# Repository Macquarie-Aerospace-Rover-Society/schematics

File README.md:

# ALL THINGS ELECTRICAL
All the schematics and manufacturing files will be located here.

If there are any requests, corrections or objections, please direct them at @sunnyshenao on the MQ rover discord.

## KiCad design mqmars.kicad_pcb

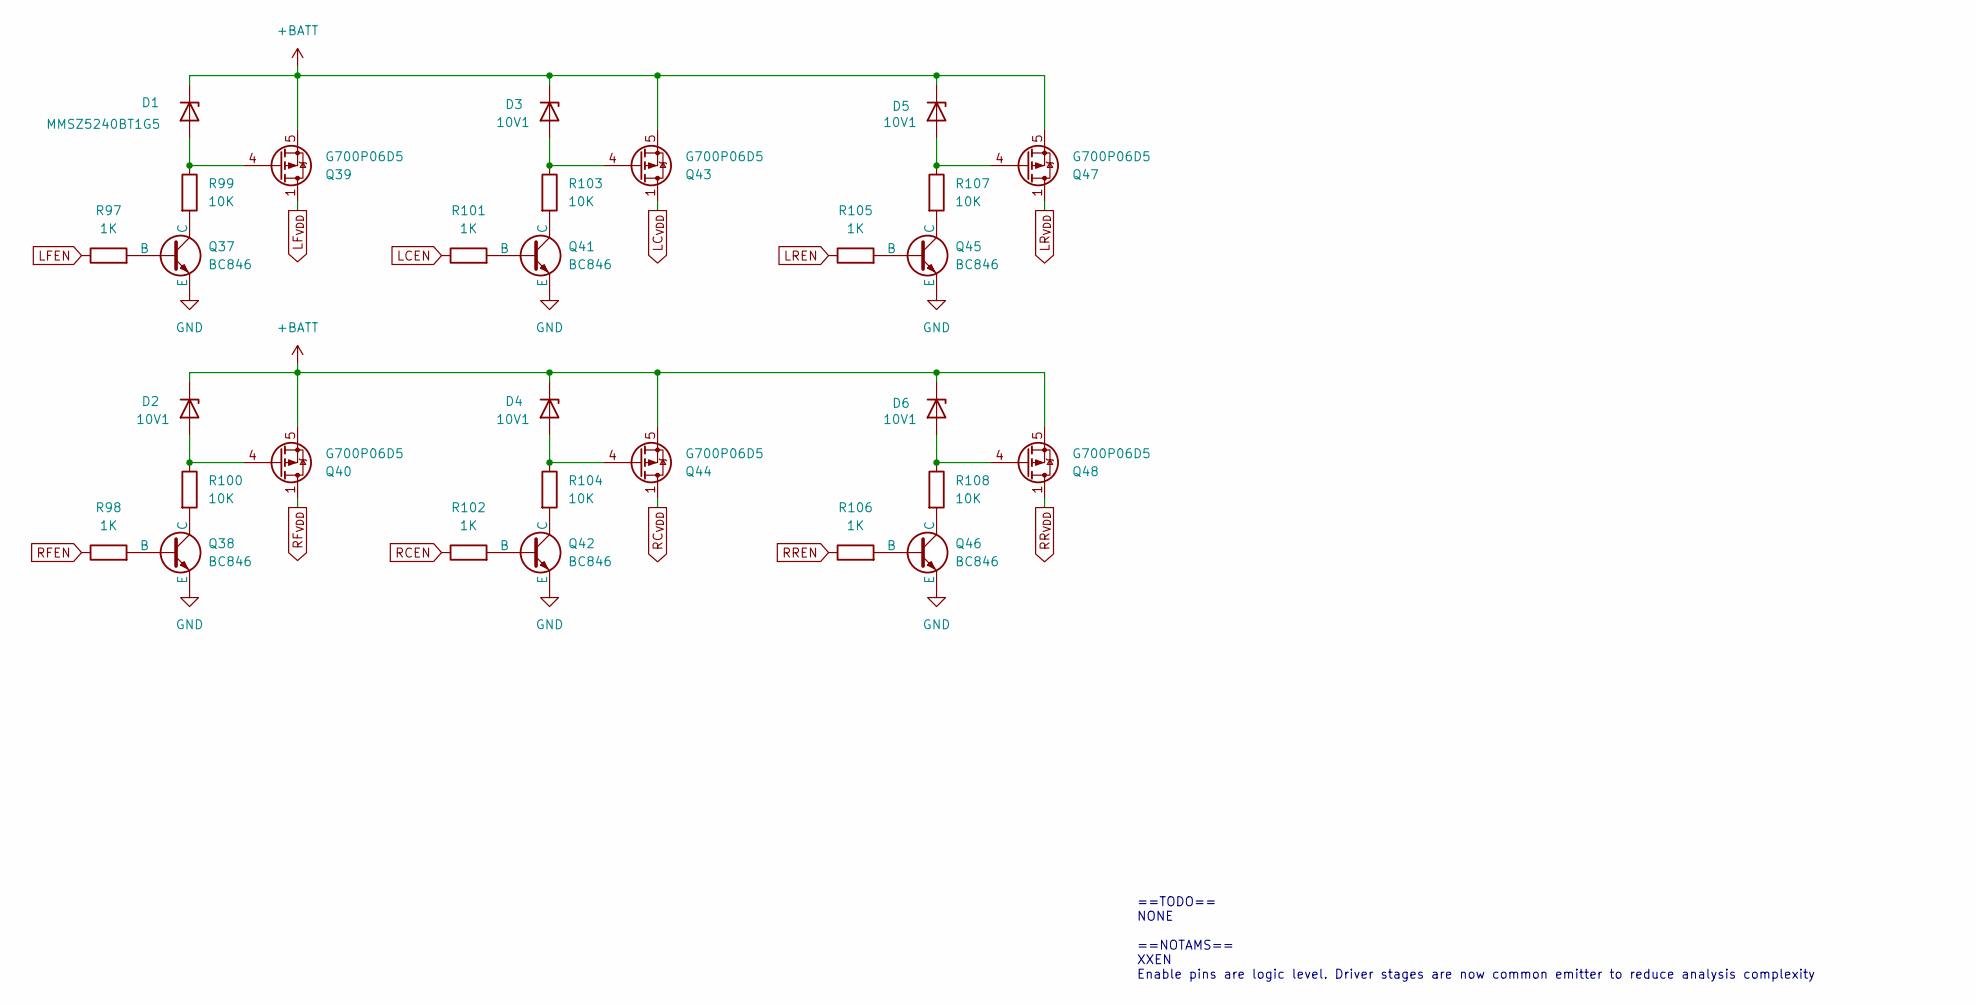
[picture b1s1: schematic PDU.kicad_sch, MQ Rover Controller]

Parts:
D1: MMSZ5240BT1G5; D_SOD-123
D2, D3, D4, D5, D6: 10V1; D_SOD-123
Q37, Q38, Q41, Q42, Q45, Q46: BC846; SOT-23
Q39, Q40, Q43, Q44, Q47, Q48: G700P06D5; PowerPAK_SO-8_Single
R97, R98, R101, R102, R105, R106: 1K; R_0201_0603Metric
R99, R100, R103, R104, R107, R108: 10K; R_1210_3225Metric

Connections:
+BATT: D1.1 (K), D2.1 (K), D3.1 (K), D4.1 (K), D5.1 (K), D6.1 (K), Q39.5 (S), Q40.5 (S), Q43.5 (S), Q44.5 (S), Q47.5 (S), Q48.5 (S); also elsewhere on the board
GND: Q37.3 (E), Q38.3 (E), Q41.3 (E), Q42.3 (E), Q45.3 (E), Q46.3 (E); also elsewhere on the board
LCEN: R101.1; also elsewhere on the board
LC_{VDD}: Q43.1 (D), Q43.2 (D), Q43.3 (D); also elsewhere on the board
LFEN: R97.1; also elsewhere on the board
LF_{VDD}: Q39.1 (D), Q39.2 (D), Q39.3 (D); also elsewhere on the board
LREN: R105.1; also elsewhere on the board
LR_{VDD}: Q47.1 (D), Q47.2 (D), Q47.3 (D); also elsewhere on the board
unnamed: D1.2 (A), Q39.4 (G), R99.1
unnamed: D2.2 (A), Q40.4 (G), R100.1
unnamed: D3.2 (A), Q43.4 (G), R103.1
unnamed: D4.2 (A), Q44.4 (G), R104.1
unnamed: D5.2 (A), Q47.4 (G), R107.1
unnamed: D6.2 (A), Q48.4 (G), R108.1
unnamed: Q37.2 (B), R97.2
unnamed: Q37.1 (C), R99.2
unnamed: Q38.2 (B), R98.2
unnamed: Q38.1 (C), R100.2
unnamed: Q41.2 (B), R101.2
unnamed: Q41.1 (C), R103.2
unnamed: Q42.2 (B), R102.2
unnamed: Q42.1 (C), R104.2
unnamed: Q45.2 (B), R105.2
unnamed: Q45.1 (C), R107.2
unnamed: Q46.2 (B), R106.2
unnamed: Q46.1 (C), R108.2
RCEN: R102.1; also elsewhere on the board
RC_{VDD}: Q44.1 (D), Q44.2 (D), Q44.3 (D); also elsewhere on the board
RFEN: R98.1; also elsewhere on the board
RF_{VDD}: Q40.1 (D), Q40.2 (D), Q40.3 (D); also elsewhere on the board
RREN: R106.1; also elsewhere on the board
RR_{VDD}: Q48.1 (D), Q48.2 (D), Q48.3 (D); also elsewhere on the board

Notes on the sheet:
==TODO== NONE ==NOTAMS== XXEN Enable pins are logic level. Driver stages are now common emitter to reduce analysis complexity

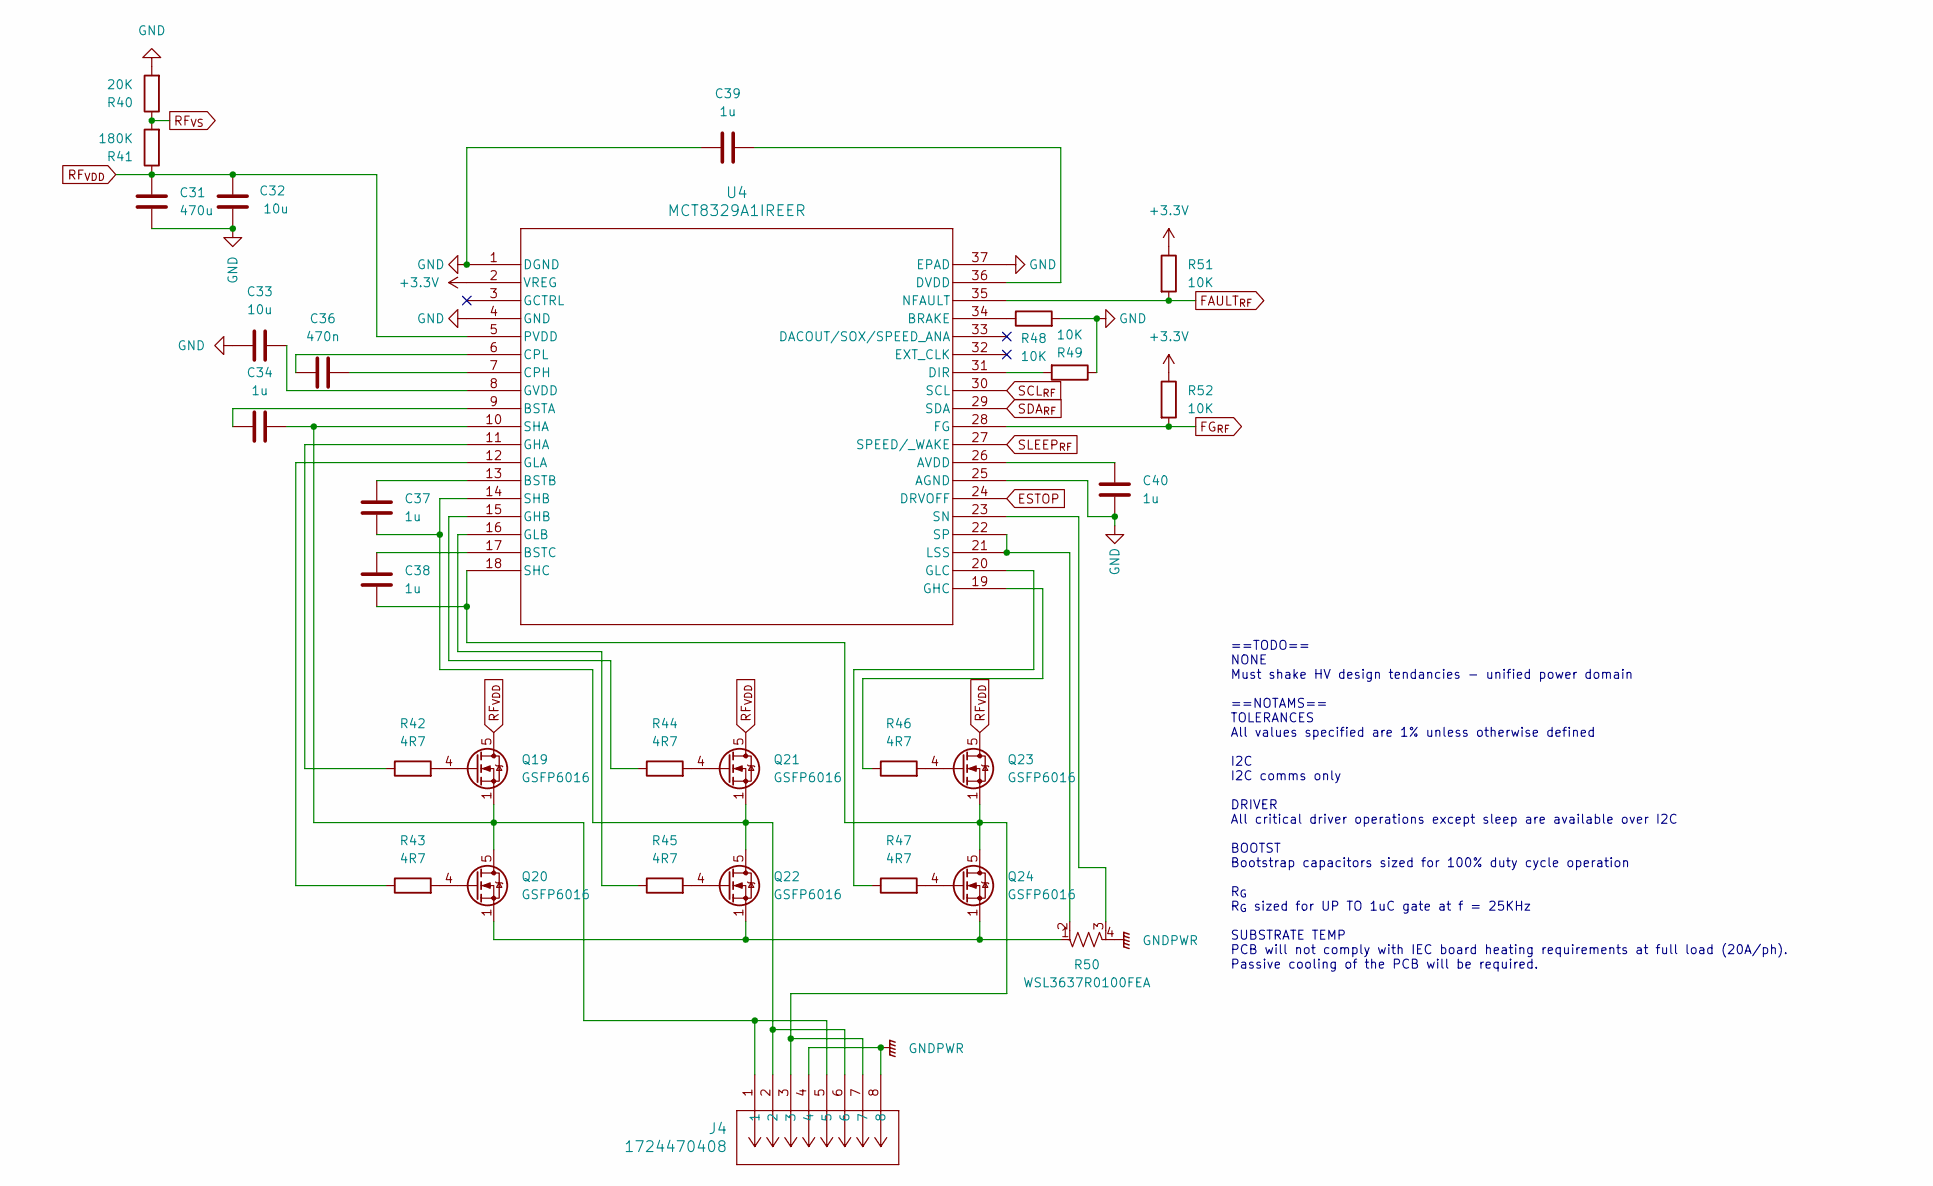
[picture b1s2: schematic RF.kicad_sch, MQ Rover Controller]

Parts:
C31: 470u; CP_Radial_D10.0mm_P5.00mm
C32: 10u; C_1210_3225Metric
C33: 10u; C_0402_1005Metric
C34, C37, C38, C39, C40: 1u; C_0201_0603Metric
C36: 470n; C_0201_0603Metric
J4: 1724470408; CONN08_1724470408_MOL
Q19, Q20, Q21, Q22, Q23, Q24: GSFP6016; PowerPAK_SO-8_Single
R40: 20K; R_0201_0603Metric
R41: 180K; R_0201_0603Metric
R42, R43, R44, R45, R46, R47: 4R7; R_0603_1608Metric
R48, R49, R51, R52: 10K; R_0201_0603Metric
R50: WSL3637R0100FEA; WSL3637_VIS
U4: MCT8329A1IREER; WQFN36_REE_TEX

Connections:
+3.3V: R51.1, R52.1, U4.2 (VREG); also elsewhere on the board
ESTOP: U4.24 (DRVOFF); also elsewhere on the board
FAULT_{RF}: R51.2, U4.35 (NFAULT); also elsewhere on the board
FG_{RF}: R52.2, U4.28 (FG)
GND: C31.2, C32.2, C33.1, C39.1, C40.1, R40.2, R48.2, R49.1, U4.1 (DGND), U4.4 (GND), U4.25 (AGND), U4.37 (EPAD); also elsewhere on the board
GNDPWR: J4.4, J4.8, R50.4; also elsewhere on the board
unnamed: Q19.4 (G), R42.2
unnamed: C34.1, J4.1, J4.5, Q19.1 (S), Q19.2 (S), Q19.3 (S), Q20.5 (D), U4.10 (SHA)
unnamed: Q20.4 (G), R43.2
unnamed: Q20.1 (S), Q20.2 (S), Q20.3 (S), Q22.1 (S), Q22.2 (S), Q22.3 (S), Q24.1 (S), Q24.2 (S), Q24.3 (S), R50.1
unnamed: Q21.4 (G), R44.2
unnamed: C37.2, J4.2, J4.6, Q21.1 (S), Q21.2 (S), Q21.3 (S), Q22.5 (D), U4.14 (SHB)
unnamed: Q22.4 (G), R45.2
unnamed: Q23.4 (G), R46.2
unnamed: C38.2, J4.3, J4.7, Q23.1 (S), Q23.2 (S), Q23.3 (S), Q24.5 (D), U4.18 (SHC)
unnamed: Q24.4 (G), R47.2
unnamed: C40.2, U4.26 (AVDD)
unnamed: R48.1, U4.34 (BRAKE)
unnamed: C34.2, U4.9 (BSTA)
unnamed: C37.1, U4.13 (BSTB)
unnamed: C38.1, U4.17 (BSTC)
unnamed: C36.1, U4.7 (CPH)
unnamed: C36.2, U4.6 (CPL)
unnamed: R49.2, U4.31 (DIR)
unnamed: C39.2, U4.36 (DVDD)
unnamed: R42.1, U4.11 (GHA)
unnamed: R44.1, U4.15 (GHB)
unnamed: R46.1, U4.19 (GHC)
unnamed: R43.1, U4.12 (GLA)
unnamed: R45.1, U4.16 (GLB)
unnamed: R47.1, U4.20 (GLC)
unnamed: C33.2, U4.8 (GVDD)
unnamed: R50.2, U4.21 (LSS), U4.22 (SP)
unnamed: R50.3, U4.23 (SN)
RF_{VDD}: C31.1, C32.1, Q19.5 (D), Q21.5 (D), Q23.5 (D), R41.1, U4.5 (PVDD); also elsewhere on the board
RF_{VS}: R40.1, R41.2; also elsewhere on the board
SCL_{RF}: U4.30 (SCL); also elsewhere on the board
SDA_{RF}: U4.29 (SDA); also elsewhere on the board
SLEEP_{RF}: U4.27 (SPEED/_WAKE)

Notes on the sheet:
==TODO== NONE Must shake HV design tendancies - unified power domain ==NOTAMS== TOLERANCES All values specified are 1% unless otherwise defined I2C I2C comms only DRIVER All critical driver operations except sleep are available over I2C BOOTST Bootstrap capacitors sized for 100% duty cycle operatio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

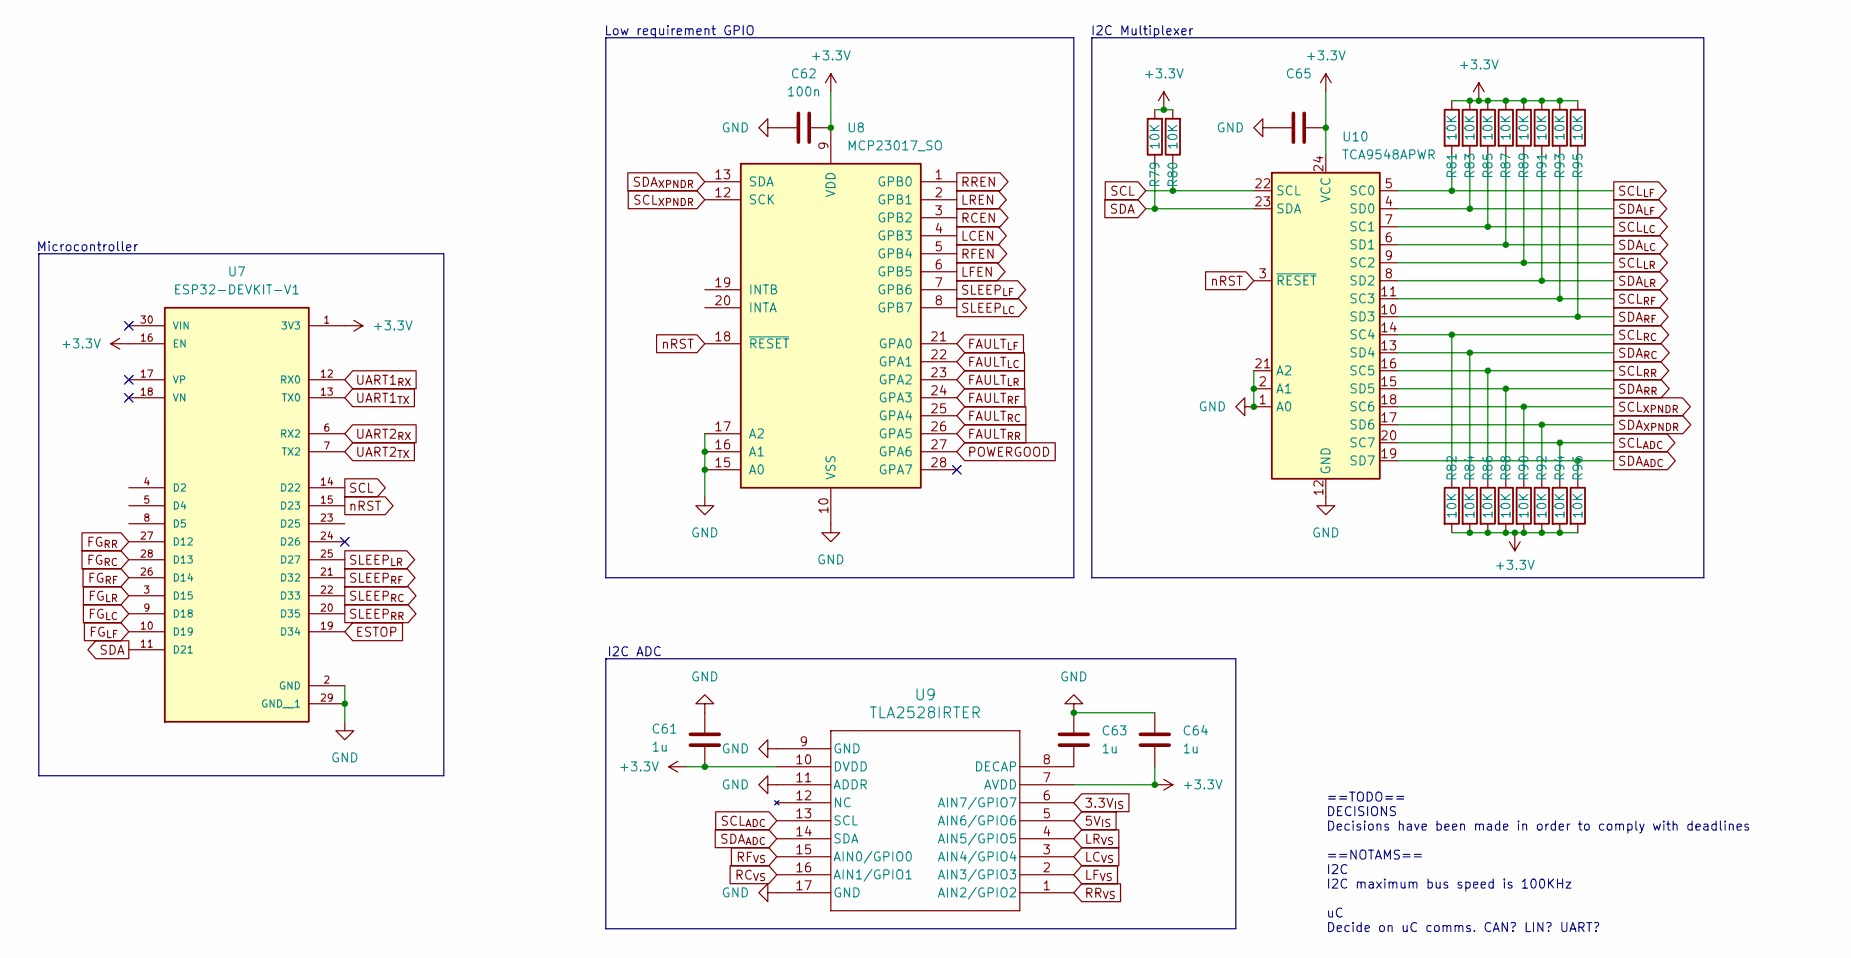
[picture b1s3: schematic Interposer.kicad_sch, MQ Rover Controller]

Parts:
C61, C63, C64: 1u; C_0201_0603Metric
C62: 100n; C_0201_0603Metric
C65: C_0201_0603Metric
R79, R80, R81, R82, R83, R84, R85, R86, R87, R88, R89, R90, R91, R92, R93, R94, R95, R96: 10K; R_0201_0603Metric
U7: ESP32-DEVKIT-V1; MODULE_ESP32_DEVKIT_V1; PARTREV N/A
U8: MCP23017_SO; SOIC-28W_7.5x17.9mm_P1.27mm
U9: TLA2528IRTER; WQFN16_RTE_TEX
U10: TCA9548APWR; TSSOP-24_4.4x7.8mm_P0.65mm

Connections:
3.3V_{IS}: U9.6 (AIN7/GPIO7); also elsewhere on the board
5V_{IS}: U9.5 (AIN6/GPIO6); also elsewhere on the board
+3.3V: C61.1, C62.2, C64.2, C65.2, R79.2, R80.2, R81.1, R82.2, R83.1, R84.2, R85.1, R86.2, R87.1, R88.2, R89.1, R90.2, R91.1, R92.2, R93.1, R94.2, R95.1, R96.2, U7.1 (3V3), U7.16 (EN), U8.9 (VDD), U9.7 (AVDD), U9.10 (DVDD), U10.24 (VCC); also elsewhere on the board
FAULT_{LC}: U8.22 (GPA1); also elsewhere on the board
FAULT_{LF}: U8.21 (GPA0); also elsewhere on the board
FAULT_{LR}: U8.23 (GPA2); also elsewhere on the board
FAULT_{RC}: U8.25 (GPA4); also elsewhere on the board
FAULT_{RF}: U8.24 (GPA3); also elsewhere on the board
FAULT_{RR}: U8.26 (GPA5); also elsewhere on the board
GND: C61.2, C62.1, C63.1, C64.1, C65.1, U7.2 (GND), U7.29 (GND__1), U8.10 (VSS), U8.15 (A0), U8.16 (A1), U8.17 (A2), U9.9 (GND), U9.11 (ADDR), U9.17 (GND), U10.1 (A0), U10.2 (A1), U10.12 (GND), U10.21 (A2); also elsewhere on the board
LCEN: U8.4 (GPB3); also elsewhere on the board
LC_{VS}: U9.3 (AIN4/GPIO4); also elsewhere on the board
LFEN: U8.6 (GPB5); also elsewhere on the board
LF_{VS}: U9.2 (AIN3/GPIO3); also elsewhere on the board
LREN: U8.2 (GPB1); also elsewhere on the board
LR_{VS}: U9.4 (AIN5/GPIO5); also elsewhere on the board
unnamed: C63.2, U9.8 (DECAP)
POWERGOOD: U8.27 (GPA6); also elsewhere on the board
RCEN: U8.3 (GPB2); also elsewhere on the board
RC_{VS}: U9.16 (AIN1/GPIO1); also elsewhere on the board
RFEN: U8.5 (GPB4); also elsewhere on the board
RF_{VS}: U9.15 (AIN0/GPIO0); also elsewhere on the board
RREN: U8.1 (GPB0); also elsewhere on the board
RR_{VS}: U9.1 (AIN2/GPIO2); also elsewhere on the board
SCL: R80.1, U7.14 (D22), U10.22 (SCL)
SCL_{ADC}: R94.1, U9.13 (SCL), U10.20 (SC7)
SCL_{LC}: R85.2, U10.7 (SC1); also elsewhere on the board
SCL_{LF}: R81.2, U10.5 (SC0); also elsewhere on the board
SCL_{LR}: R89.2, U10.9 (SC2); also elsewhere on the board
SCL_{RC}: R82.1, U10.14 (SC4); also elsewhere on the board
SCL_{RF}: R93.2, U10.11 (SC3); also elsewhere on the board
SCL_{RR}: R86.1, U10.16 (SC5); also elsewhere on the board
SCL_{XPNDR}: R90.1, U8.12 (SCK), U10.18 (SC6)
SDA: R79.1, U7.11 (D21), U10.23 (SDA)
SDA_{ADC}: R96.1, U9.14 (SDA), U10.19 (SD7)
SDA_{LC}: R87.2, U10.6 (SD1); also elsewhere on the board
SDA_{LF}: R83.2, U10.4 (SD0); also elsewhere on the board
SDA_{LR}: R91.2, U10.8 (SD2); also elsewhere on the board
SDA_{RC}: R84.1, U10.13 (SD4); also elsewhere on the board
SDA_{RF}: R95.2, U10.10 (SD3); also elsewhere on the board
SDA_{RR}: R88.1, U10.15 (SD5); also elsewhere on the board
SDA_{XPNDR}: R92.1, U8.13 (SDA), U10.17 (SD6)
SLEEP_{LC}: U8.8 (GPB7); also elsewhere on the board
SLEEP_{LF}: U8.7 (GPB6); also elsewhere on the board
nRST: U7.15 (D23), U8.18 (~RESET), U10.3 (~RESET)

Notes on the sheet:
==TODO== DECISIONS Decisions have been made in order to comply with deadlines ==NOTAMS== I2C I2C maximum bus speed is 100KHz uC Decide on uC comms. CAN? LIN? UART?
I2C Multiplexer
Microcontroller
Low requirement GPIO
I2C ADC

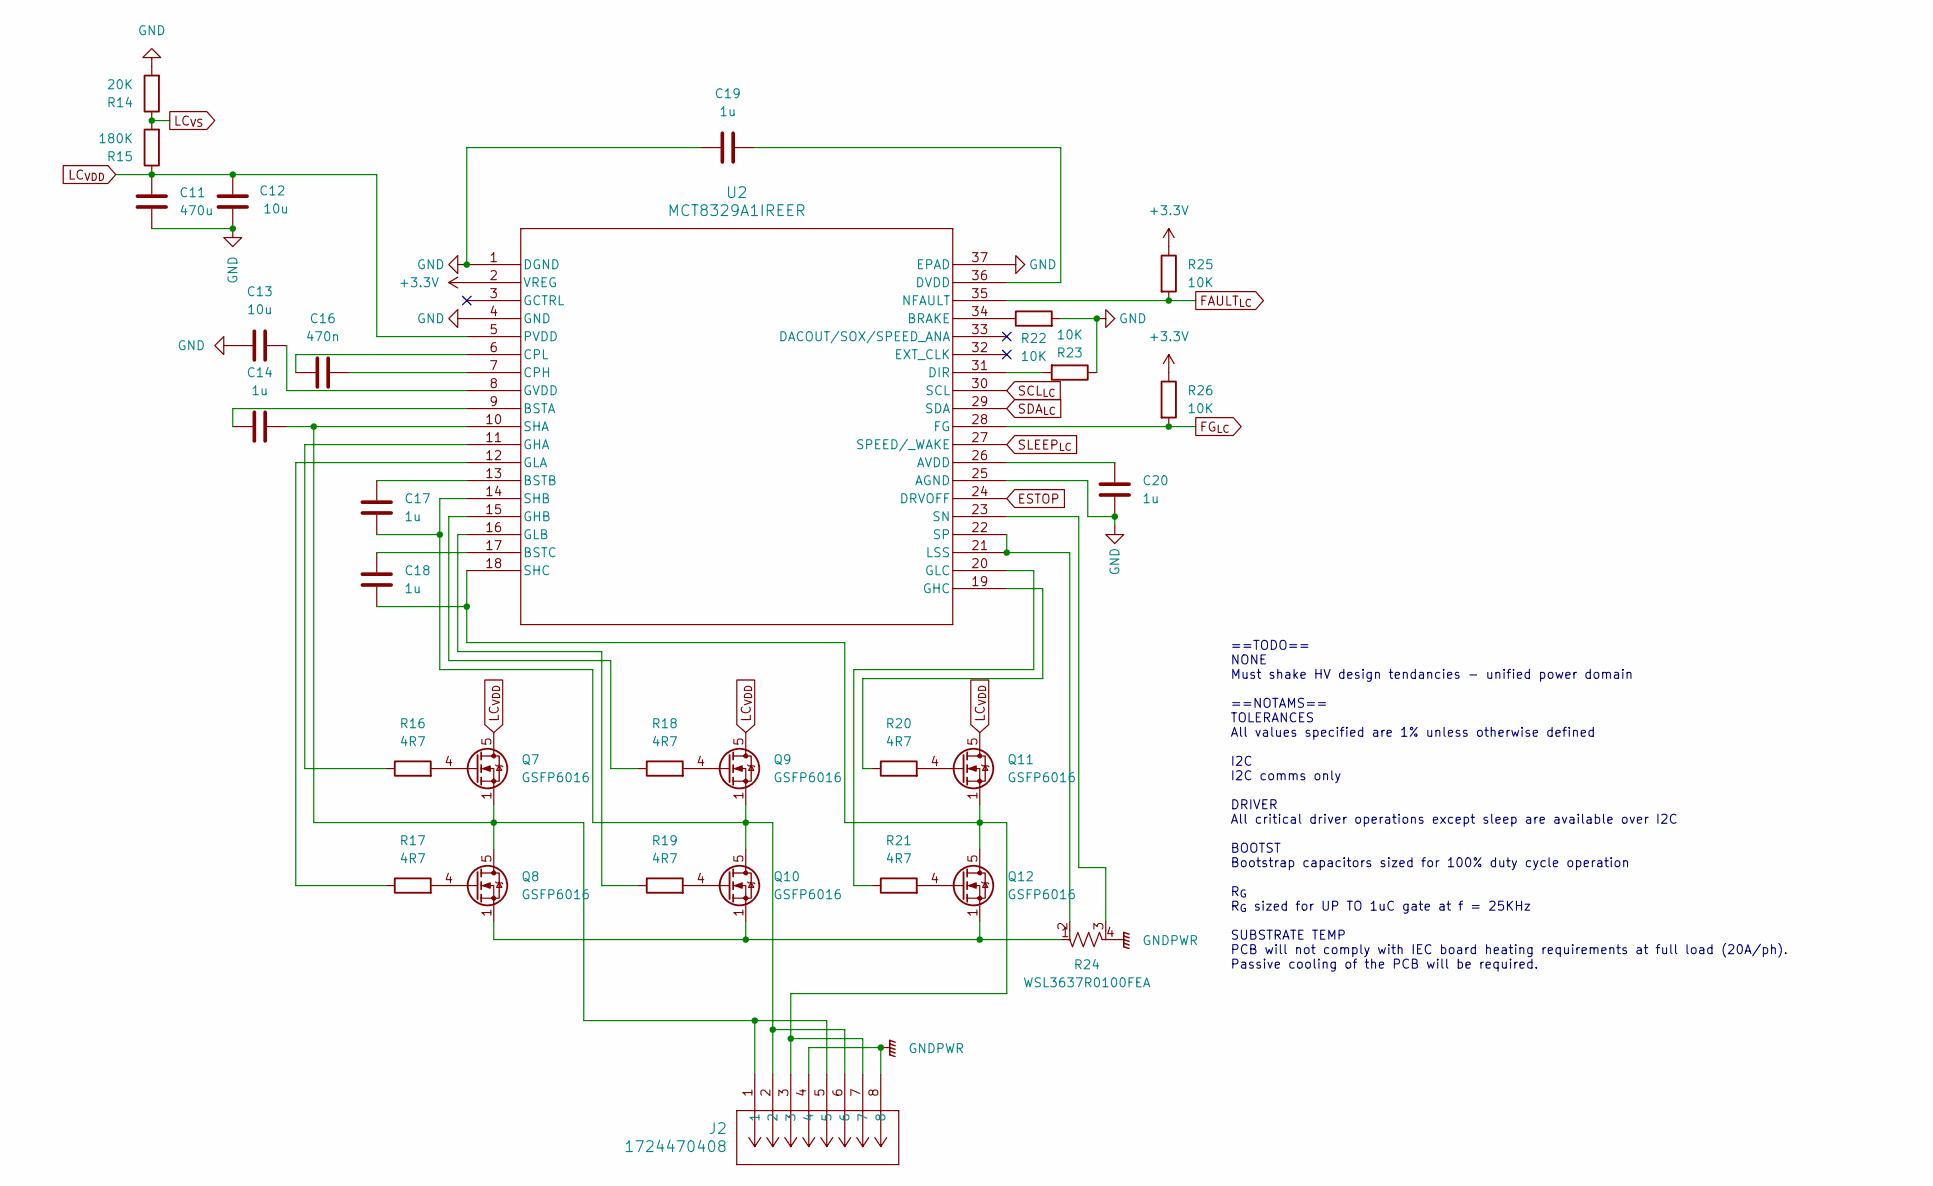
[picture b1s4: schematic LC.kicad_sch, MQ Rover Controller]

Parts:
C11: 470u; CP_Radial_D10.0mm_P5.00mm
C12: 10u; C_1210_3225Metric
C13: 10u; C_0402_1005Metric
C14, C17, C18, C19, C20: 1u; C_0201_0603Metric
C16: 470n; C_0201_0603Metric
J2: 1724470408; CONN08_1724470408_MOL
Q7, Q8, Q9, Q10, Q11, Q12: GSFP6016; PowerPAK_SO-8_Single
R14: 20K; R_0201_0603Metric
R15: 180K; R_0201_0603Metric
R16, R17, R18, R19, R20, R21: 4R7; R_0603_1608Metric
R22, R23, R25, R26: 10K; R_0201_0603Metric
R24: WSL3637R0100FEA; WSL3637_VIS
U2: MCT8329A1IREER; WQFN36_REE_TEX

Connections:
+3.3V: R25.1, R26.1, U2.2 (VREG); also elsewhere on the board
ESTOP: U2.24 (DRVOFF); also elsewhere on the board
FAULT_{LC}: R25.2, U2.35 (NFAULT); also elsewhere on the board
FG_{LC}: R26.2, U2.28 (FG)
GND: C11.2, C12.2, C13.1, C19.1, C20.1, R14.2, R22.2, R23.1, U2.1 (DGND), U2.4 (GND), U2.25 (AGND), U2.37 (EPAD); also elsewhere on the board
GNDPWR: J2.4, J2.8, R24.4; also elsewhere on the board
LC_{VDD}: C11.1, C12.1, Q7.5 (D), Q9.5 (D), Q11.5 (D), R15.1, U2.5 (PVDD); also elsewhere on the board
LC_{VS}: R14.1, R15.2; also elsewhere on the board
unnamed: Q7.4 (G), R16.2
unnamed: C14.1, J2.1, J2.5, Q7.1 (S), Q7.2 (S), Q7.3 (S), Q8.5 (D), U2.10 (SHA)
unnamed: Q8.4 (G), R17.2
unnamed: Q9.4 (G), R18.2
unnamed: C17.2, J2.2, J2.6, Q9.1 (S), Q9.2 (S), Q9.3 (S), Q10.5 (D), U2.14 (SHB)
unnamed: Q10.4 (G), R19.2
unnamed: Q8.1 (S), Q8.2 (S), Q8.3 (S), Q10.1 (S), Q10.2 (S), Q10.3 (S), Q12.1 (S), Q12.2 (S), Q12.3 (S), R24.1
unnamed: Q11.4 (G), R20.2
unnamed: C18.2, J2.3, J2.7, Q11.1 (S), Q11.2 (S), Q11.3 (S), Q12.5 (D), U2.18 (SHC)
unnamed: Q12.4 (G), R21.2
unnamed: C20.2, U2.26 (AVDD)
unnamed: R22.1, U2.34 (BRAKE)
unnamed: C14.2, U2.9 (BSTA)
unnamed: C17.1, U2.13 (BSTB)
unnamed: C18.1, U2.17 (BSTC)
unnamed: C16.1, U2.7 (CPH)
unnamed: C16.2, U2.6 (CPL)
unnamed: R23.2, U2.31 (DIR)
unnamed: C19.2, U2.36 (DVDD)
unnamed: R16.1, U2.11 (GHA)
unnamed: R18.1, U2.15 (GHB)
unnamed: R20.1, U2.19 (GHC)
unnamed: R17.1, U2.12 (GLA)
unnamed: R19.1, U2.16 (GLB)
unnamed: R21.1, U2.20 (GLC)
unnamed: C13.2, U2.8 (GVDD)
unnamed: R24.2, U2.21 (LSS), U2.22 (SP)
unnamed: R24.3, U2.23 (SN)
SCL_{LC}: U2.30 (SCL); also elsewhere on the board
SDA_{LC}: U2.29 (SDA); also elsewhere on the board
SLEEP_{LC}: U2.27 (SPEED/_WAKE); also elsewhere on the board

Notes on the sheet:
==TODO== NONE Must shake HV design tendancies - unified power domain ==NOTAMS== TOLERANCES All values specified are 1% unless otherwise defined I2C I2C comms only DRIVER All critical driver operations except sleep are available over I2C BOOTST Bootstrap capacitors sized for 100% duty cycle operatio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

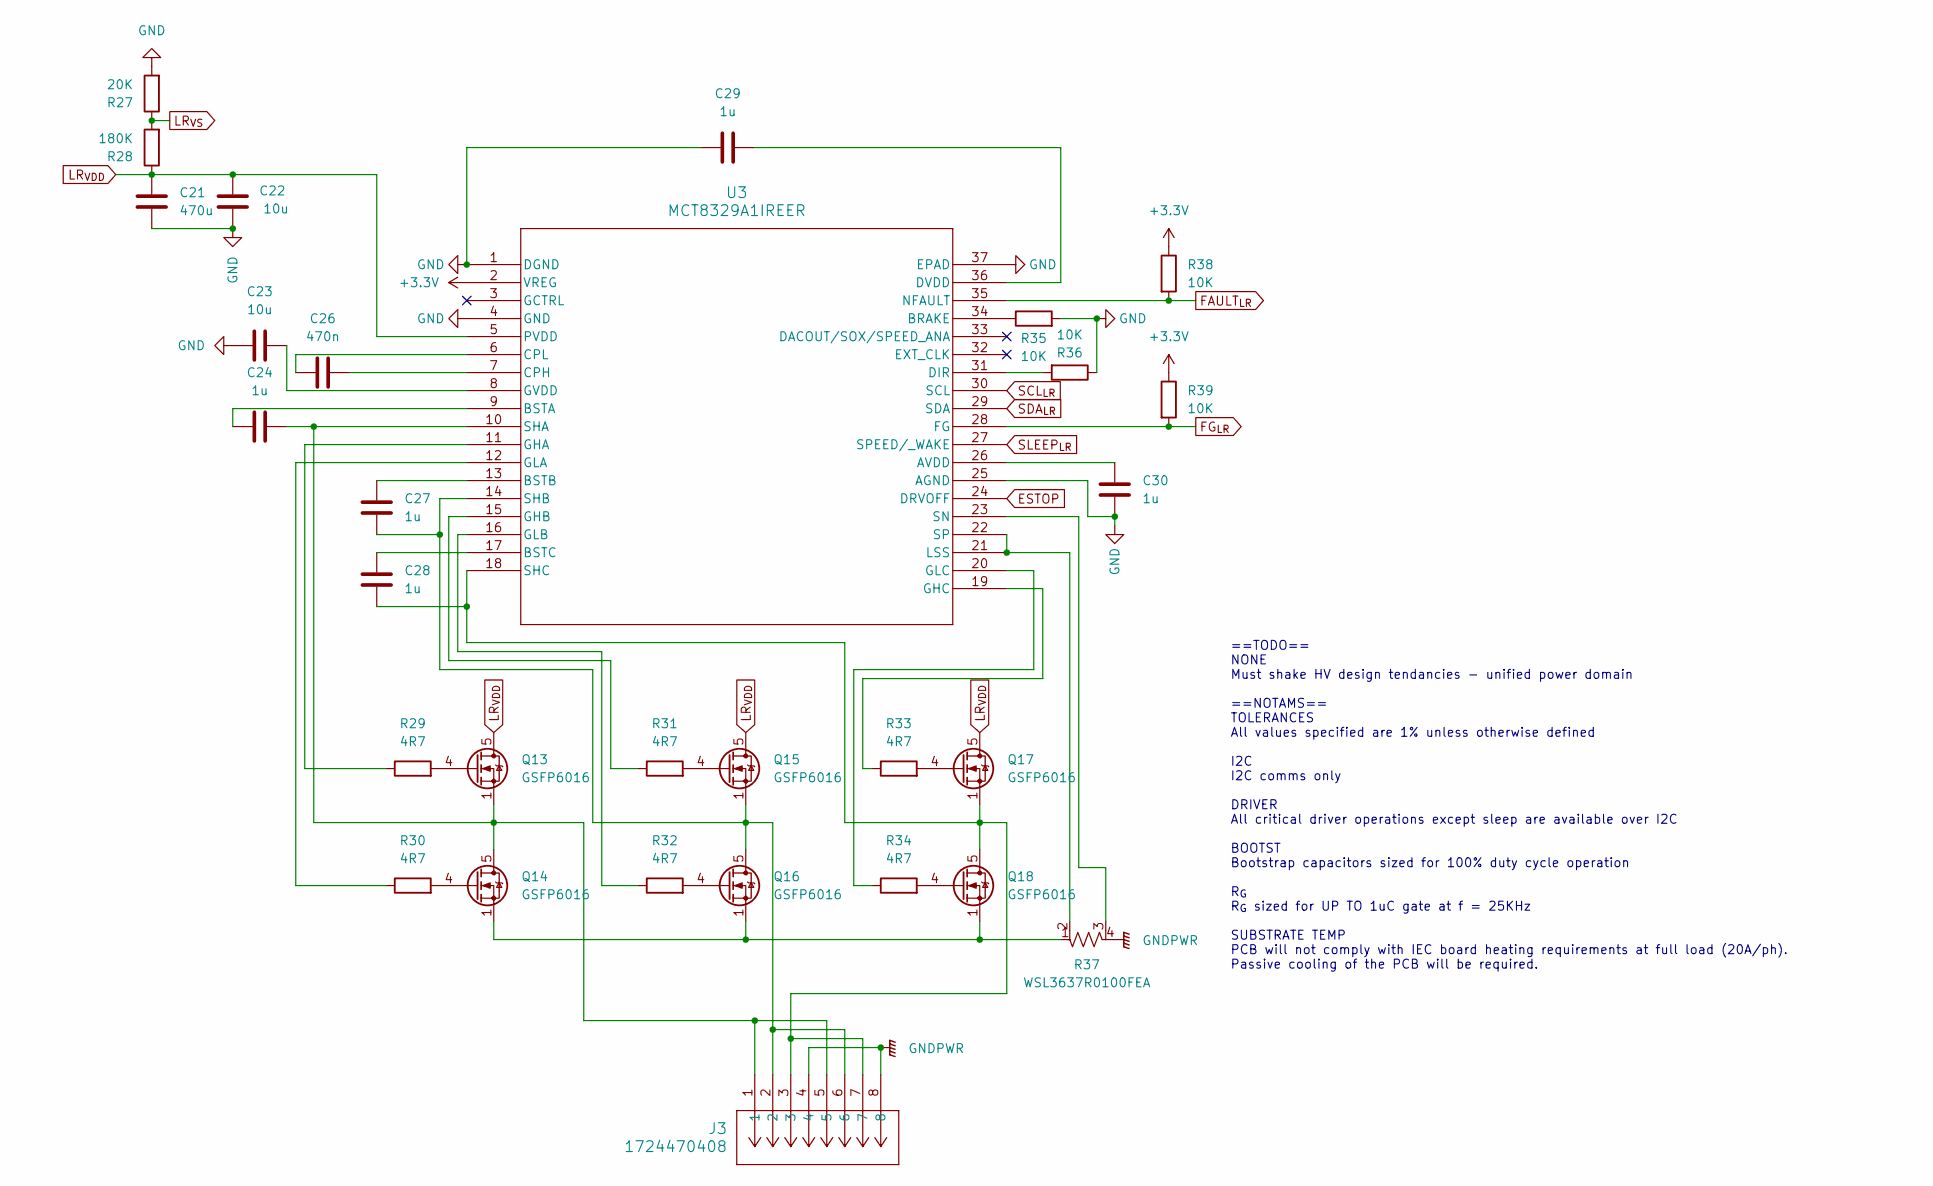
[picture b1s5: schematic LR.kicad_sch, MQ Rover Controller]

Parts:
C21: 470u; CP_Radial_D10.0mm_P5.00mm
C22: 10u; C_1210_3225Metric
C23: 10u; C_0402_1005Metric
C24, C27, C28, C29, C30: 1u; C_0201_0603Metric
C26: 470n; C_0201_0603Metric
J3: 1724470408; CONN08_1724470408_MOL
Q13, Q14, Q15, Q16, Q17, Q18: GSFP6016; PowerPAK_SO-8_Single
R27: 20K; R_0201_0603Metric
R28: 180K; R_0201_0603Metric
R29, R30, R31, R32, R33, R34: 4R7; R_0603_1608Metric
R35, R36, R38, R39: 10K; R_0201_0603Metric
R37: WSL3637R0100FEA; WSL3637_VIS
U3: MCT8329A1IREER; WQFN36_REE_TEX

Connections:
+3.3V: R38.1, R39.1, U3.2 (VREG); also elsewhere on the board
ESTOP: U3.24 (DRVOFF); also elsewhere on the board
FAULT_{LR}: R38.2, U3.35 (NFAULT); also elsewhere on the board
FG_{LR}: R39.2, U3.28 (FG)
GND: C21.2, C22.2, C23.1, C29.1, C30.1, R27.2, R35.2, R36.1, U3.1 (DGND), U3.4 (GND), U3.25 (AGND), U3.37 (EPAD); also elsewhere on the board
GNDPWR: J3.4, J3.8, R37.4; also elsewhere on the board
LR_{VDD}: C21.1, C22.1, Q13.5 (D), Q15.5 (D), Q17.5 (D), R28.1, U3.5 (PVDD); also elsewhere on the board
LR_{VS}: R27.1, R28.2; also elsewhere on the board
unnamed: Q13.4 (G), R29.2
unnamed: C24.1, J3.1, J3.5, Q13.1 (S), Q13.2 (S), Q13.3 (S), Q14.5 (D), U3.10 (SHA)
unnamed: Q14.4 (G), R30.2
unnamed: Q14.1 (S), Q14.2 (S), Q14.3 (S), Q16.1 (S), Q16.2 (S), Q16.3 (S), Q18.1 (S), Q18.2 (S), Q18.3 (S), R37.1
unnamed: Q15.4 (G), R31.2
unnamed: C27.2, J3.2, J3.6, Q15.1 (S), Q15.2 (S), Q15.3 (S), Q16.5 (D), U3.14 (SHB)
unnamed: Q16.4 (G), R32.2
unnamed: Q17.4 (G), R33.2
unnamed: C28.2, J3.3, J3.7, Q17.1 (S), Q17.2 (S), Q17.3 (S), Q18.5 (D), U3.18 (SHC)
unnamed: Q18.4 (G), R34.2
unnamed: C30.2, U3.26 (AVDD)
unnamed: R35.1, U3.34 (BRAKE)
unnamed: C24.2, U3.9 (BSTA)
unnamed: C27.1, U3.13 (BSTB)
unnamed: C28.1, U3.17 (BSTC)
unnamed: C26.1, U3.7 (CPH)
unnamed: C26.2, U3.6 (CPL)
unnamed: R36.2, U3.31 (DIR)
unnamed: C29.2, U3.36 (DVDD)
unnamed: R29.1, U3.11 (GHA)
unnamed: R31.1, U3.15 (GHB)
unnamed: R33.1, U3.19 (GHC)
unnamed: R30.1, U3.12 (GLA)
unnamed: R32.1, U3.16 (GLB)
unnamed: R34.1, U3.20 (GLC)
unnamed: C23.2, U3.8 (GVDD)
unnamed: R37.2, U3.21 (LSS), U3.22 (SP)
unnamed: R37.3, U3.23 (SN)
SCL_{LR}: U3.30 (SCL); also elsewhere on the board
SDA_{LR}: U3.29 (SDA); also elsewhere on the board
SLEEP_{LR}: U3.27 (SPEED/_WAKE)

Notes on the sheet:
==TODO== NONE Must shake HV design tendancies - unified power domain ==NOTAMS== TOLERANCES All values specified are 1% unless otherwise defined I2C I2C comms only DRIVER All critical driver operations except sleep are available over I2C BOOTST Bootstrap capacitors sized for 100% duty cycle operatio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

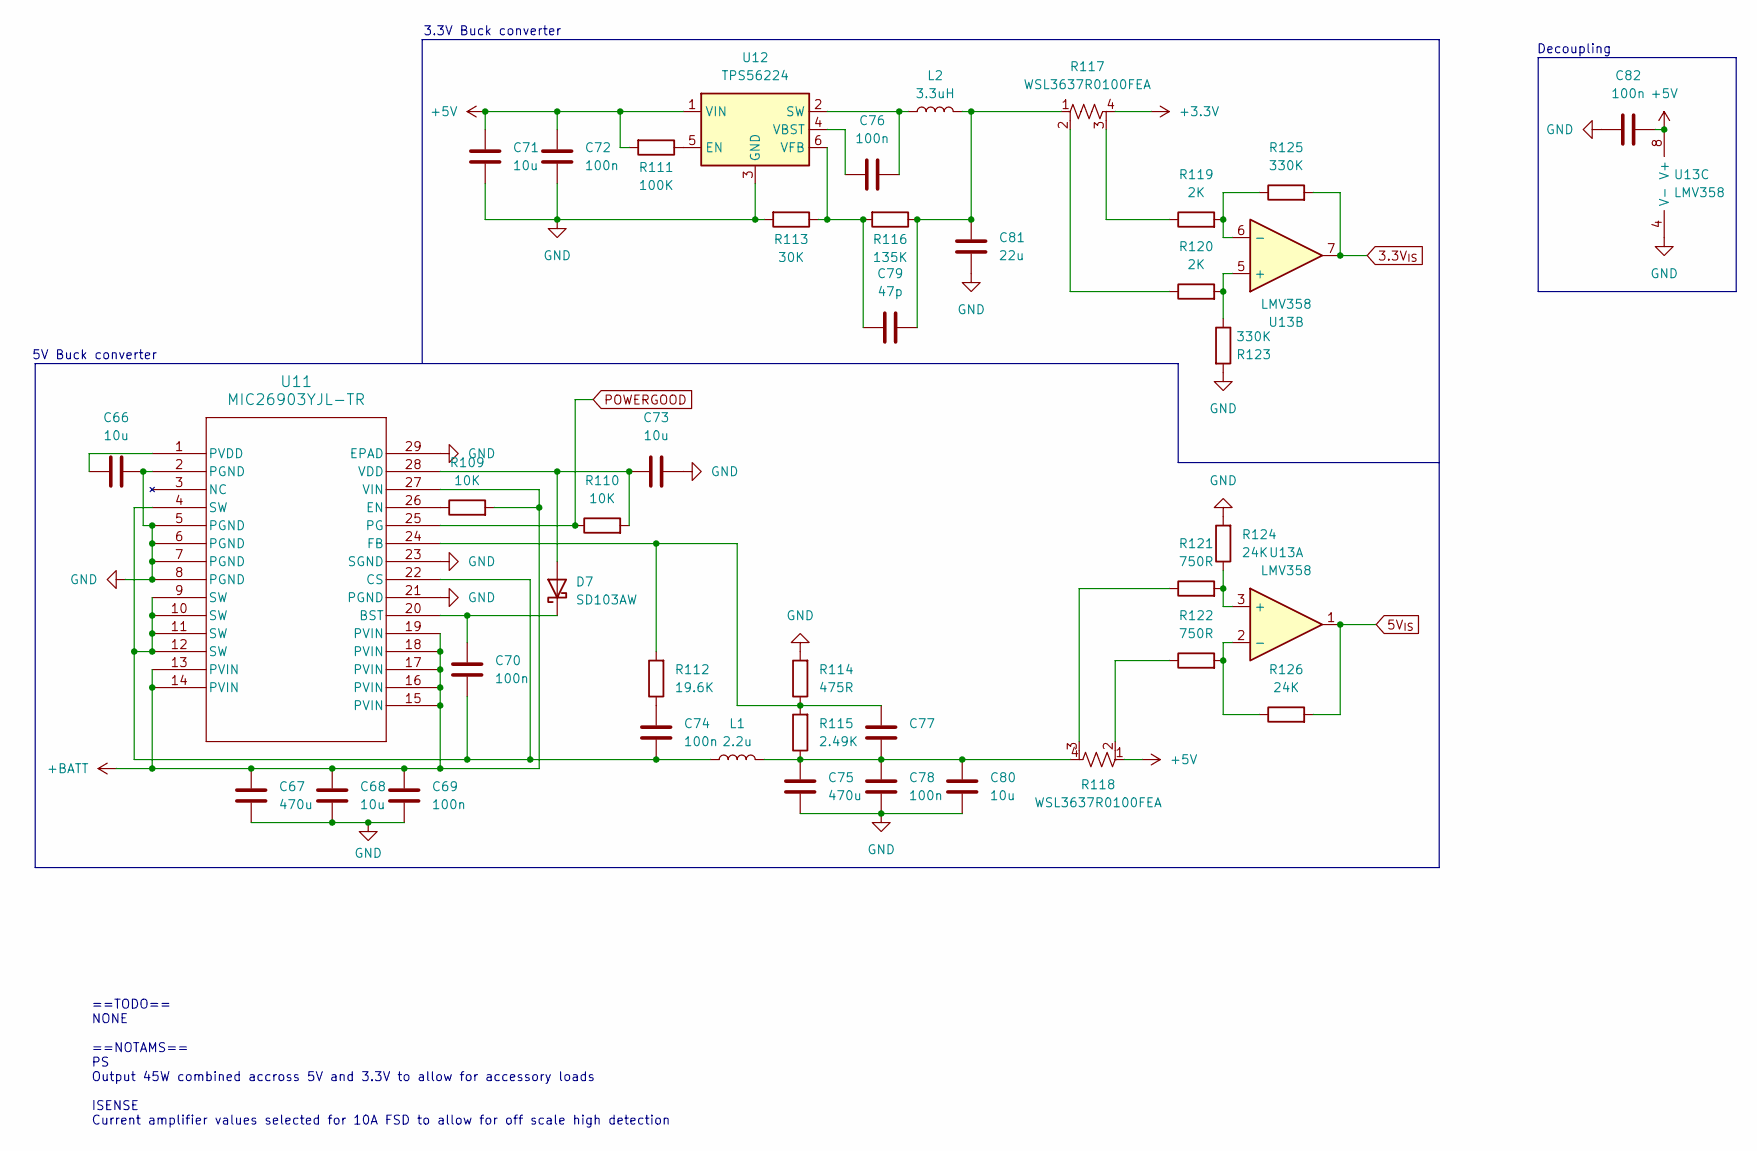
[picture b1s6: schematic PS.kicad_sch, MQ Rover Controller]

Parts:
C66, C71, C73: 10u; C_0402_1005Metric
C67, C75: 470u; C_0603_1608Metric
C68, C80: 10u; C_0603_1608Metric
C69, C74, C78: 100n; C_0603_1608Metric
C70, C72, C76, C82: 100n; C_0201_0603Metric
C77: C_0201_0603Metric
C79: 47p; C_0201_0603Metric
C81: 22u; C_0603_1608Metric
D7: SD103AW; D_SOD-123
L1: 2.2u; L_Bourns_SRN8040TA
L2: 3.3uH; L_Coilcraft_LPS3314
R109, R110: 10K; R_0603_1608Metric
R111: 100K; R_0603_1608Metric
R112: 19.6K; R_0603_1608Metric
R113: 30K; R_0603_1608Metric
R114: 475R; R_0603_1608Metric
R115: 2.49K; R_0603_1608Metric
R116: 135K; R_0603_1608Metric
R117, R118: WSL3637R0100FEA; WSL3637_VIS
R119, R120: 2K; R_0603_1608Metric
R121, R122: 750R; R_0603_1608Metric
R123, R125: 330K; R_0603_1608Metric
R124, R126: 24K; R_0603_1608Metric
U11: MIC26903YJL-TR; MLF28_5X6_MCH
U12: TPS56224; SOT-563
U13: LMV358; VSSOP-8_3x3mm_P0.65mm

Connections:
3.3V_{IS}: R125.2, U13.7; also elsewhere on the board
5V_{IS}: R126.2, U13.1; also elsewhere on the board
+3.3V: R117.4; also elsewhere on the board
+5V: C71.1, C72.1, C82.2, R111.2, R118.1, U12.1 (VIN), U13.8 (V+)
+BATT: C67.2, C68.2, C69.2, R109.2, U11.13 (PVIN), U11.14 (PVIN), U11.15 (PVIN), U11.16 (PVIN), U11.17 (PVIN), U11.18 (PVIN), U11.19 (PVIN), U11.27 (VIN); also elsewhere on the board
GND: C66.1, C67.1, C68.1, C69.1, C71.2, C72.2, C73.1, C75.1, C78.1, C80.1, C81.2, C82.1, R113.2, R114.2, R123.2, R124.2, U11.2 (PGND), U11.5 (PGND), U11.6 (PGND), U11.7 (PGND), U11.8 (PGND), U11.21 (PGND), U11.23 (SGND), U11.29 (EPAD), U12.3 (GND), U13.4 (V-); also elsewhere on the board
unnamed: C74.1, R112.1
unnamed: C75.2, C77.2, C78.2, C80.2, L1.2, R115.1, R118.4
unnamed: C79.1, C81.1, L2.2, R116.1, R117.1
unnamed: C73.2, D7.2 (A), R110.2, U11.28 (VDD)
unnamed: C70.1, D7.1 (K), U11.20 (BST)
unnamed: R117.2, R120.1
unnamed: R117.3, R119.1
unnamed: R118.2, R122.1
unnamed: R118.3, R121.1
unnamed: C70.2, C74.2, L1.1, U11.4 (SW), U11.9 (SW), U11.10 (SW), U11.11 (SW), U11.12 (SW), U11.22 (CS)
unnamed: R109.1, U11.26 (EN)
unnamed: C77.1, R112.2, R114.1, R115.2, U11.24 (FB)
unnamed: C66.2, U11.1 (PVDD)
unnamed: R111.1, U12.5 (EN)
unnamed: C76.1, L2.1, U12.2 (SW)
unnamed: C76.2, U12.4 (VBST)
unnamed: C79.2, R113.1, R116.2, U12.6 (VFB)
unnamed: R121.2, R124.1, U13.3 (+)
unnamed: R122.2, R126.1, U13.2 (-)
unnamed: R120.2, R123.1, U13.5 (+)
unnamed: R119.2, R125.1, U13.6 (-)
POWERGOOD: R110.1, U11.25 (PG); also elsewhere on the board

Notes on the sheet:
==TODO== NONE ==NOTAMS== PS Output 45W combined accross 5V and 3.3V to allow for accessory loads ISENSE Current amplifier values selected for 10A FSD to allow for off scale high detection
5V Buck converter
3.3V Buck converter
Decoupling
